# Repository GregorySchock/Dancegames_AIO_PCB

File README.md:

# Dancegames_AIO_PCB
PCB that can control all necessary aspects of hooking up a set of sensors to a PC in order to play games such as DDR and PIU

Made to have an arduino pro micro (or compatible) board inserted in the corner. Also has a set of buttons and LEDs to assist in calibration, if using velostat sensors that support automatic calibration routines. See my other repos for that code, if interested.

Designed in KiCad. A set of 5 boards is pretty cheap if purchased from a site like JLCPCB, just upload the GERBERS to their order form. For the rest of the components, see the BOM file for product numbers.

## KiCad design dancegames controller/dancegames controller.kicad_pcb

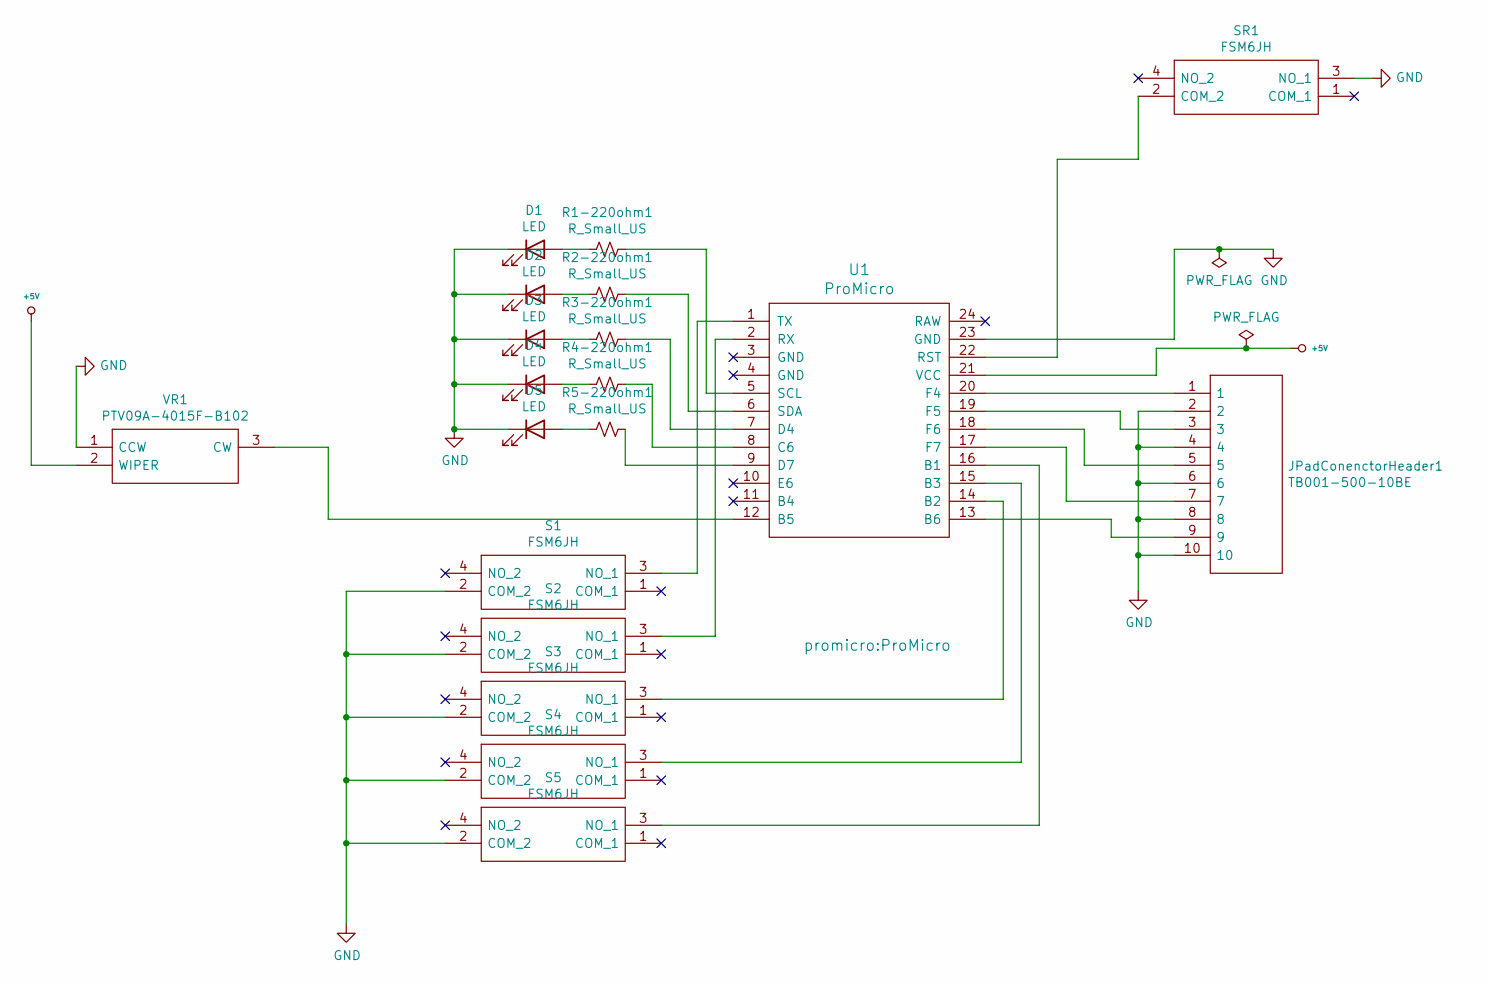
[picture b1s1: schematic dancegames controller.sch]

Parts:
D1, D2, D3, D4, D5: LED; LED_D4.0mm_1.25mmhole
JPadConenctorHeader1: TB001-500-10BE; SHDR10W100P0X500_1X10_5000X900X1250P; Mouser Part Number 490-TB001-500-10BE
R1-220ohm1, R2-220ohm1, R3-220ohm1, R4-220ohm1, R5-220ohm1: R_Small_US; R_Axial_DIN0207_L6.3mm_D2.5mm_P7.62mm_Horizontal
S1, S2, S3, S4, S5: FSM6JH; Mouser Part Number 506-FSM6JH
SR1: FSM6JH; Mouser Part Number 506-FSM6JH
U1: ProMicro
VR1: PTV09A-4015F-B102; PTV09A4020FB103; Mouser Part Number 652-PTV09A-4015FB102

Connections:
+5V: U1.21 (VCC), VR1.2 (WIPER)
GND: D1.1 (K), D2.1 (K), D3.1 (K), D4.1 (K), D5.1 (K), JPadConenctorHeader1.2, JPadConenctorHeader1.4, JPadConenctorHeader1.6, JPadConenctorHeader1.8, JPadConenctorHeader1.10, S1.2 (COM_2), S2.2 (COM_2), S3.2 (COM_2), S4.2 (COM_2), S5.2 (COM_2), SR1.3 (NO_1), U1.23 (GND), VR1.1 (CCW)
unnamed: D1.2 (A), R1-220ohm1.1
unnamed: D2.2 (A), R2-220ohm1.1
unnamed: D3.2 (A), R3-220ohm1.1
unnamed: D4.2 (A), R4-220ohm1.1
unnamed: D5.2 (A), R5-220ohm1.1
unnamed: JPadConenctorHeader1.1, U1.20 (F4)
unnamed: JPadConenctorHeader1.3, U1.19 (F5)
unnamed: JPadConenctorHeader1.5, U1.18 (F6)
unnamed: JPadConenctorHeader1.7, U1.17 (F7)
unnamed: JPadConenctorHeader1.9, U1.13 (B6)
unnamed: R1-220ohm1.2, U1.5 (SCL)
unnamed: R2-220ohm1.2, U1.6 (SDA)
unnamed: R3-220ohm1.2, U1.7 (D4)
unnamed: R4-220ohm1.2, U1.8 (C6)
unnamed: R5-220ohm1.2, U1.9 (D7)
unnamed: S1.3 (NO_1), U1.1 (TX)
unnamed: S2.3 (NO_1), U1.2 (RX)
unnamed: S3.3 (NO_1), U1.14 (B2)
unnamed: S4.3 (NO_1), U1.15 (B3)
unnamed: S5.3 (NO_1), U1.16 (B1)
unnamed: SR1.2 (COM_2), U1.22 (RST)
unnamed: U1.12 (B5), VR1.3 (CW)

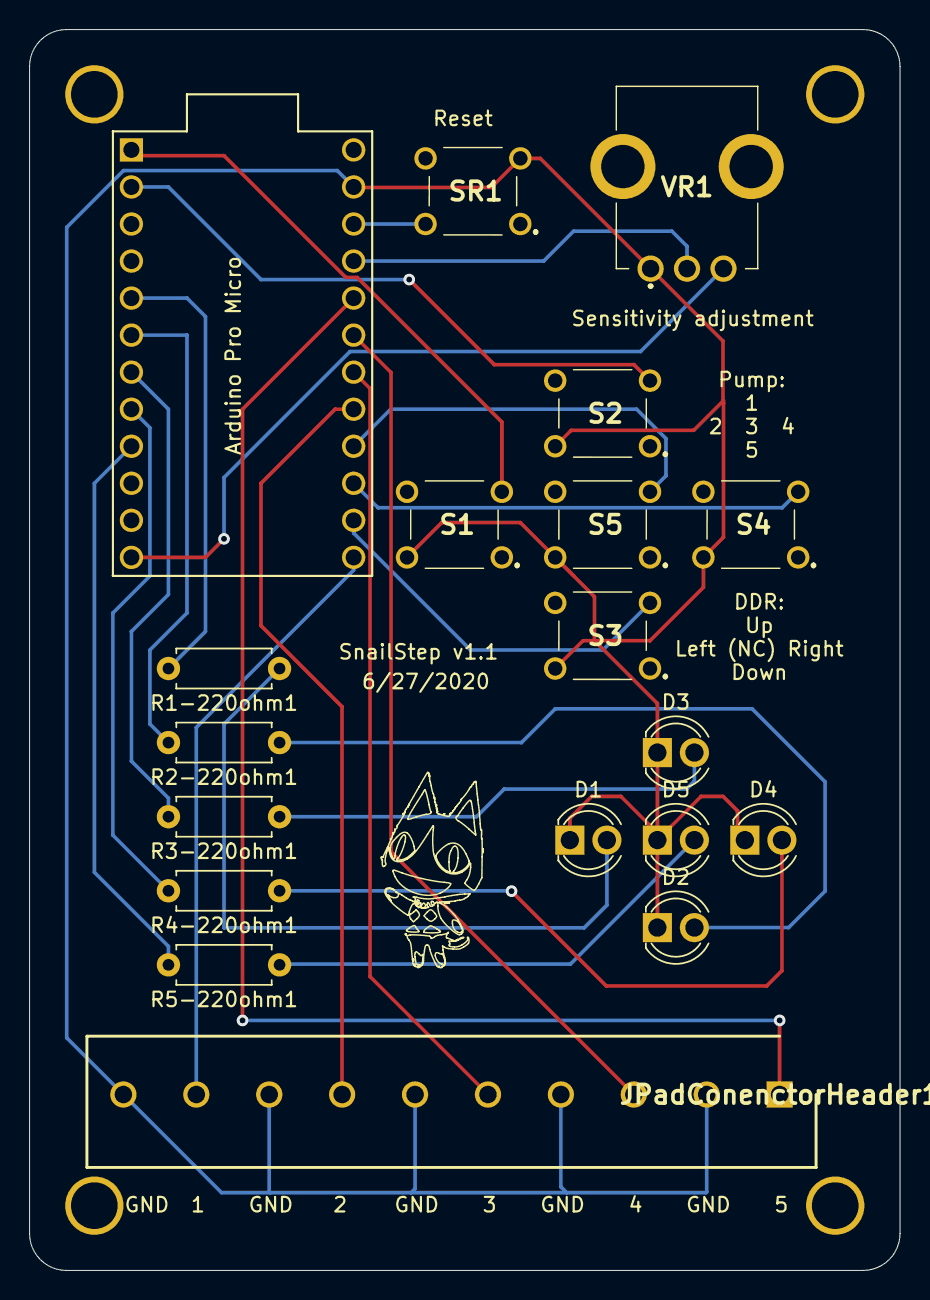
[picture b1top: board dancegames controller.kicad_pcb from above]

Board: 2 copper layers, 59.7 x 85.1 mm, 23 parts (0 on the bottom side), 24 nets.

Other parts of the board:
HOLE_M3, HOLE_M3#2, HOLE_M3#3, HOLE_M3#4: VAL**; HOLE_M3

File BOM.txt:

If you'd like to do a 1:1 recreation of what I've made, these are the part numbers for the components I used. All parts were purchased on Mouser, with the exception of the pro micro and its PCB leg headers (both sourced via aliexpress).
I'll provide the manufacturer product numbers for each component, rather than the mouser number, should you prefer another vendor such as DigiKey or LCSC.
1 PCB (from JLC, using the board files here)
1 Potentiometer - PTV09A-4015F-B102
6 tactile switches - FSM6JH
1 10 hole terminal block - TB001-500-10BE
5 through hole resistors (I used 220 ohm but I'd recommend going higher, mine are almost blindingly bright)- CFR-25JT-52-220R
5 LEDs (Accidentally ordered oval ones, but just about any 5v LEDs will work just fine)- C4SMF-BJF-CR24Q4T2

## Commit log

2020-06-27 Dance game controller PCB
